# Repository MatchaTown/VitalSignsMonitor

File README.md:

Semua file pendukung penelitian termasuk kode program, desain PCB, dan rancangan fisik perangkat.

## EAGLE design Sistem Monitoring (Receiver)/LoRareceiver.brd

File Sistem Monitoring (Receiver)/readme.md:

Pendukung kebutuhan Sistem Monitoring Kesehatan dengan LoRa (Receiver)

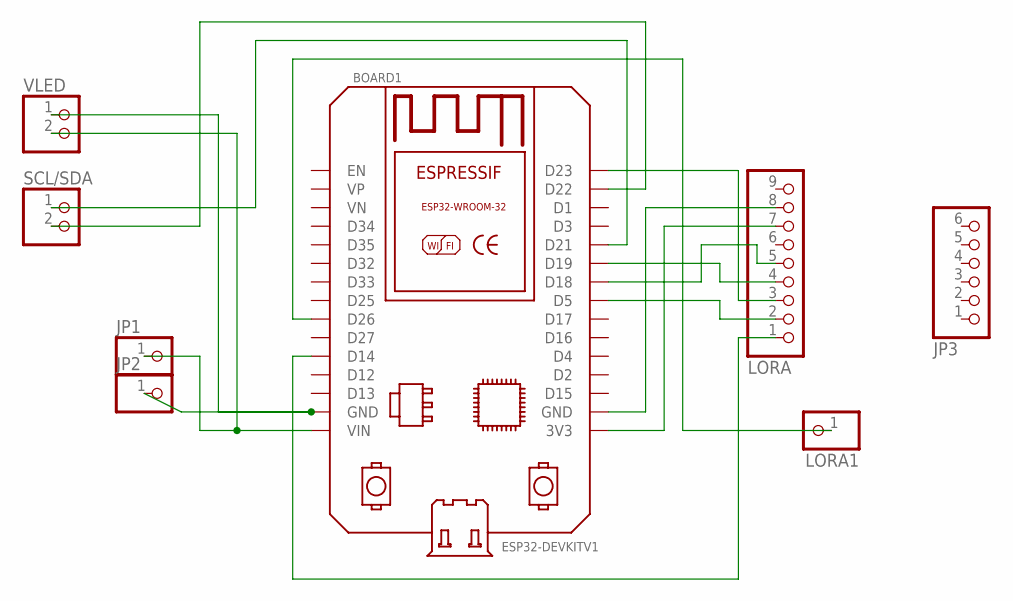
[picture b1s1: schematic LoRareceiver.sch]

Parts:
BOARD1: ESP32DEVKITV1; ESP32-DEVKITV1
JP1, JP2: PINHD-1X1; 1X01
JP3: PINHD-1X6; 1X06
LORA: PINHD-1X9; 1X09-BIG
LORA1: PINHD-1X1; 1X01
SCL/SDA: PINHD-1X2; 1X02
VLED: PINHD-1X2; 1X02

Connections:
unnamed: BOARD1.D14, LORA.1
unnamed: BOARD1.D5, LORA.2
unnamed: BOARD1.D23, LORA.3
unnamed: BOARD1.D19, LORA.4
unnamed: BOARD1.D18, LORA.5
unnamed: BOARD1.D26, LORA1.1
unnamed: BOARD1.3V3, LORA.7
unnamed: BOARD1.GND@1 (GND), LORA.8
unnamed: BOARD1.VIN, JP1.1, VLED.2
unnamed: BOARD1.GND, JP2.1, VLED.1
unnamed: BOARD1.D22, SCL/SDA.2
unnamed: BOARD1.D21, SCL/SDA.1

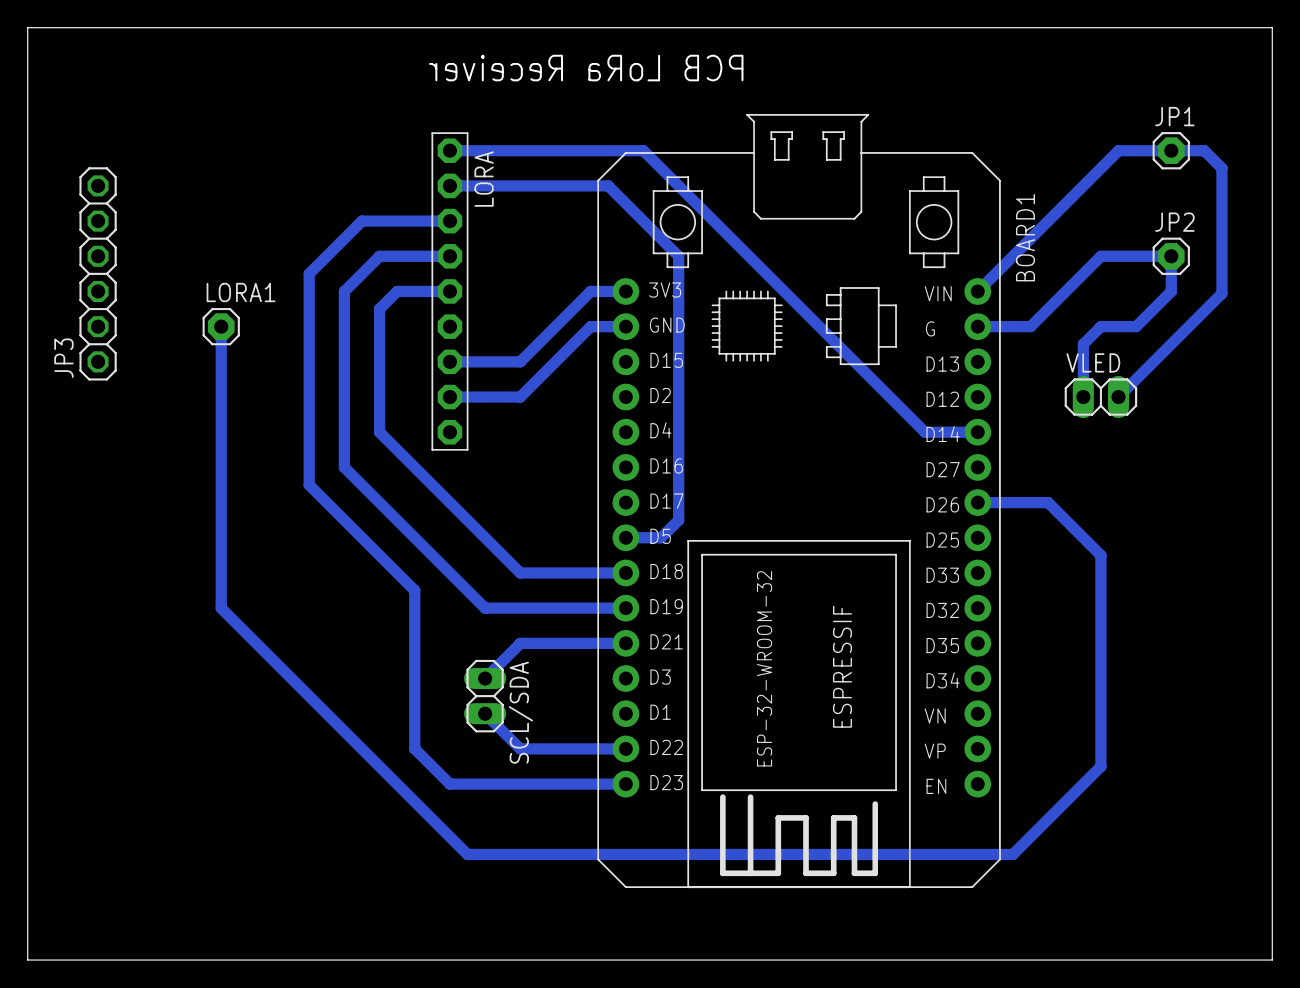
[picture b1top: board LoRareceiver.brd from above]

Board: 2 copper layers, 89.8 x 67.3 mm, 8 parts (0 on the bottom side), 12 nets.

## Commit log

2025-07-19 PCB Design
2025-07-19 Rename Transmiter-final-performa-lebih-cepat.ino to Kode Program Main Device (transmitter)
    kode program
2025-07-19 Rename Kode Program Main Device (transmitter) to as
2025-07-19 kode program
2025-07-19 desain PCB
2025-07-19 diagram skematik (wiring)
2025-07-19 Skematik Diagram (wiring rangkaian)
2025-07-19 Diagram Skematik (wiring rangkaian)
2025-07-19 Desain 3D Body Box
2025-07-19 Desain 3D Tutup Box
2025-07-19 Json Kode NodeRed
2025-07-19 Program ESP32 Receiver
2025-07-19 Program Apps Scripts Google Spreadsheets
2025-07-19 LoRa Schematic Rangakaian
2025-07-19 Board Rangkaian
2025-07-19 Program Pendukung Sistem Monitoring
